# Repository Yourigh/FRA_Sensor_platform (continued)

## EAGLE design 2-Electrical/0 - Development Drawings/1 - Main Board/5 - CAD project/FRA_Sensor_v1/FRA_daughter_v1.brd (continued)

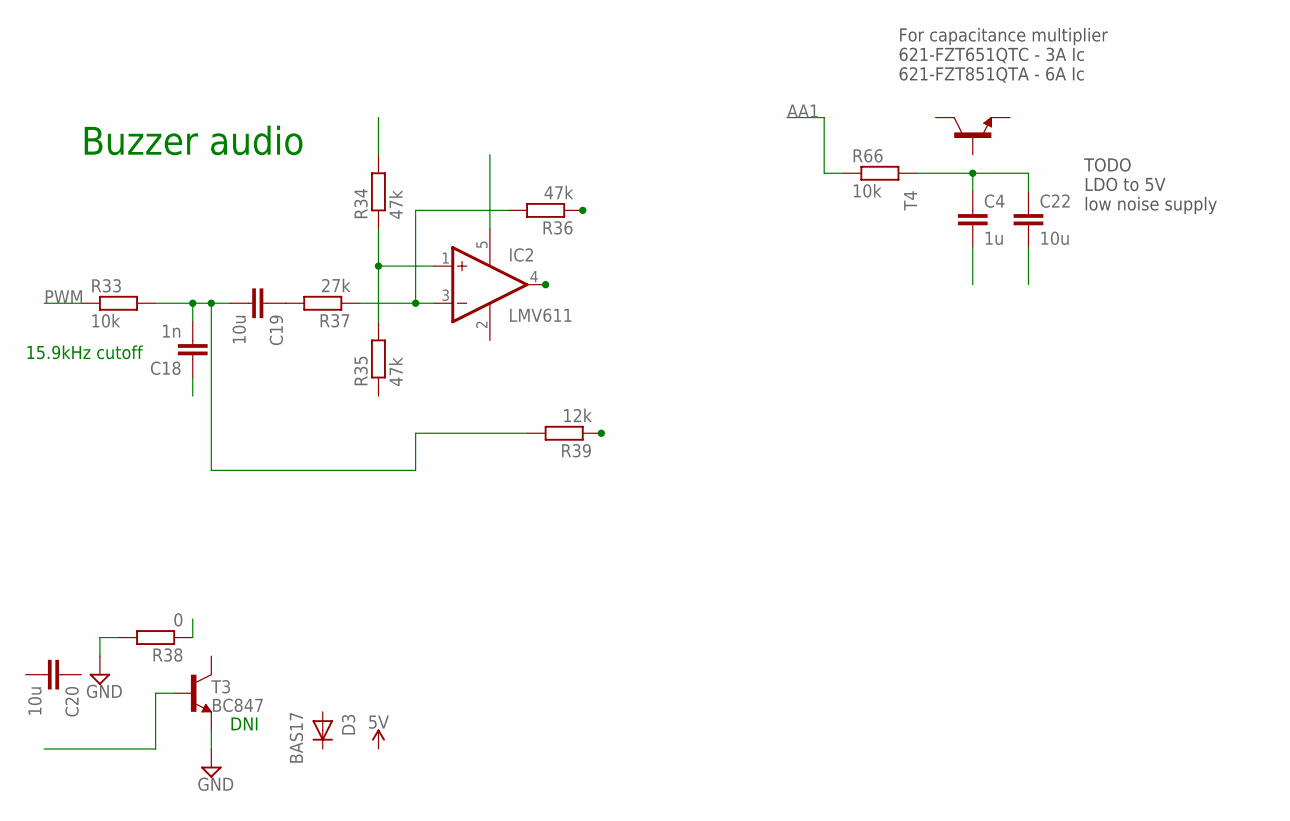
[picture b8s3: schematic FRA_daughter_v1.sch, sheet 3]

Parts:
C4: 1u; C0603K
C18: 1n; C0603K
C19, C20, C22: 10u; C0603K
D3: BAS17; SOT23
IC2: LMV611; SC70-5L
R33, R66: 10k; R0603
R34, R35, R36: 47k; R0603
R37: 27k; R0603
R38: 0; R0603
R39: 12k; R0603
T3: BC847; SOT23
T4: -NPN-SOT223; SOT223

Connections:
AA1: R66.1
GND: R38.2, T3.2 (E); also elsewhere on the board
unnamed: C4.1, C22.1, R66.2
unnamed: R39.1, T3.1 (B)
unnamed: IC2.1 (+IN), R34.1, R35.2
unnamed: IC2.3 (-IN), R36.2, R37.1
unnamed: C19.1, R37.2
unnamed: IC2.4 (OUT), R36.1
unnamed: C18.2, C19.2, R33.2, R39.2
PWM: R33.1
V-: IC2.2 (V-)

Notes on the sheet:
15.9kHz cutoff
Buzzer audio
DNI
For capacitance multiplier 621-FZT651QTC - 3A Ic 621-FZT851QTA - 6A Ic
TODO LDO to 5V low noise supply

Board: 2 copper layers, 34 parts (0 on the bottom side), 16 nets, no tracks yet.

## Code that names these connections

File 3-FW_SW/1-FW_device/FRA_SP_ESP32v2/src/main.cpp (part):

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#include <esp_task_wdt.h>

//custom pins
#define PIN_ETH_INT 36 //was 2, changed due to FW loading problems
#define PIN_ETH_NRST 4
#define PIN_LED 16
#define PIN_SD_CS  17  // SD chip select pin
#define PIN_SDA 21
#define PIN_SCL 22
#define PIN_ETH_CS 23
#define PIN_FAN 25
#define PIN_TP8 26 //used as fake SDA for real SDA line manipulation
#define PIN_TP9 27
#define PIN_BTN1 34
#define PIN_TP7 36
#define PIN_TP6 39
//custom parameters
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
void setup(){
  error_code[0] = 0;
  pinMode(PIN_BTN1,INPUT);
  attachInterrupt(digitalPinToInterrupt(PIN_BTN1), ISR_BTN1, FALLING);
  pinMode(PIN_ETH_INT,INPUT);
  pinMode(PIN_ETH_NRST,OUTPUT);
  digitalWrite(PIN_ETH_NRST,0);
  pinMode(PIN_LED,OUTPUT); //LED on final HW
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  esp_efuse_read_mac(chipid);
  chipid[5]++; //use MAC address for ETH one larger than WiFi MAC (WiFi MAC is chip ID)
  // Change 'SS' to your Slave Select pin, if you arn't using the default pin
  if (ether.begin(sizeof Ethernet::buffer, chipid, PIN_ETH_CS) == 0){
    Serial.println(F("Failed to access Ethernet controller"));
    log_error_code(1);
  }
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  // Initialize at the highest speed supported by the board that is
  // not over 50 MHz. Try a lower speed if SPI errors occur.
  use_sd = 1;
  if (!sd.begin(PIN_SD_CS, SD_SCK_MHZ(20))) {  //SPI clock , 50MHz or 40M does not wrok, 20M ok, 
    sd.initErrorHalt(); //halt turned off, but will give logs to serial
    use_sd=0;
    log_error_code(3);
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  uint32_t adc_period_ms = 1000; //every X ms 
  uint8_t adc_PGA_setting[3][4]; //ADC is first index, ch second
  int16_t adc_result_raw[3][4]; //result [ADC][channel]
  uint32_t meas_sample_number = 0; //0 is measurement not active, from 1 on - sample number
  uint8_t port0_check;
  uint8_t port1_check;
  uint8_t conf_set = 0; // raw received configuration set byte
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    //this must be called for ethercard functions to work. 
    //Returns Length of received data. If non-zero, something is coming.
    if (UDP_read_flag == 0) //if receive buffer ready for data, check if thre is incoming DTG
      if (digitalRead(PIN_ETH_INT)==0){ //if interrupt of incoming data or want to send data
        ether.packetLoop(ether.packetReceive()); //Returns Length of received data. If non-zero, something is coming.
      }
      //data were already processed and put into receiveUDP_buffer.
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        } 
        if (uint16_t(millis()) > (startms + 30000)){break;}  //30s timeout
        
        if (digitalRead(PIN_BTN1)){break;} //released button
        
        if (millis()-startms < 1000){
          //PRINTDEBUG("Pressed under 1s, nothing happens\n");
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
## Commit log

2019-05-03 UDP demo working
2019-05-04 block diagram
2019-05-04 project setup, 2 sensors in library
2019-05-04 sensor data
2019-05-05 TGS2611 integration
2019-05-06 programming interface ready
2019-05-07 project setup esp32
2019-05-08 connection update, debugger setup-now working
2019-05-08 ESP32v2 debugger running, UDP receiving
2019-05-08 not working project copy deleted
2019-05-10 SCH update
2019-05-12 power circuits
2019-05-14 UDP sender done
2019-05-18 SD card connected
2019-05-22 dev and sd
    mac address changed
    other sample testing
    sd card example setup
2019-05-22 gitignore update
2019-05-24 SD card logging test working
    SPI speed had to be decreased
2019-05-24 placment drafts
2019-05-25 write time analysis
2019-05-25 digital sensors interface
2019-05-26 VI and esp communication
2019-05-28 labview ACKs
2019-06-04 sch and layiout
2019-06-04 jtag layout
2019-06-05 power layouts
2019-06-09 sch cap miltuplier add
2019-06-16 sensor datasheets
2019-06-19 datasheets, sch update
2019-06-24 ldo addded
2019-06-27 sch update
    layout, od powerm SPIs,
2019-07-12 sch update layout update
2019-07-13 layout done,
2019-07-17 SD and ethernet merged
2019-07-17 resources update
2019-07-18 gpio expander init and all low functions
2019-07-18 adc integrated, 2 ADCs tested
2019-07-18 define custom pins, added broadcast frist for announcement of unit
2019-07-20 announcements, io expander, ...
2019-07-20 docs
2019-07-24 power reports done, interrupt ethernet..
2019-07-25 boad update v2
2019-07-25 error code array instead one value
2019-07-26 error report fixed and sw reset done
2019-07-27 fixed network, ADC begin
2019-07-29 sch main final touches
2019-07-30 sensor board sch and layout
2019-07-31 BOM updates, labview
2019-08-01 sd card logging done
2019-08-02 Light sensor integrated
2019-08-06 updates
    amonia sensor
    preparation for LMP91000
    ADC1 address changed to match V4 board
2019-08-07 data saving fixes, ADC address changed
2019-08-09 dev for LMP91000
2019-08-09 sensor board update, main VI update
2019-08-16 hw design updates
2019-08-17 amonia sensor tuning
2019-08-18 TGS board update
2019-08-18 electrochemical board design
2019-08-19 updates spec
2019-08-20 programing procedure, elchem board
2019-08-20 flash guide
2019-08-20 LMP code align
2019-08-20 versioning start
2019-08-20 full SD card check
2019-08-20 cleanup
2019-08-20 csv sync to git
2019-08-21 legends fix
2019-08-22 sensor tests
2019-08-23 sensor elchem testing, reports, code update
2019-08-23 electrochemical sensors test results
2019-08-27 data processing, orders review, tests, elchem pcb RE CE swap
2019-08-29 mhm01 board
2019-09-03 BOM updates
2019-09-04 manufacuting pics
2019-09-04 incorrect pics removed
2019-09-07 labview miltiple unit selection
2019-09-07 update of conf. sets
2019-09-10 MHM labview script update
2019-10-04 data converter work
2019-10-05 data converster from labview log done
2019-10-07 converter update
2019-10-08 converter to app specific values
2019-10-10 baseline converter
2019-10-10 converter SD card log too
2019-10-29 silkscreen update
2019-11-01 converter build exe
2019-11-02 V1.4 update conf set
2019-11-06 build exe for logger pc app
2019-11-06 bugfix, logger exe release path to DATA folder
2019-11-06 bug fix A1.3 REFCN register
2019-11-23 bug fix app spec converter
2019-11-30 added sdfat, searching for issues
2019-11-30 CS ETH pin change
2019-11-30 removed restart on EEPROM init fail
    even if eeprom fails to init, things seem to work well.
2019-11-30 LW app, runtime bux fix error database
2019-12-04 button stop measurement fcn, static fallback IP, V1.7 release
2019-12-04 added pics
2019-12-04 resized images
2019-12-04 images to readme
2019-12-06 3d export
2019-12-06 3D model created
2019-12-14 ME box project setup
2020-03-04 junction board
2020-03-04 manuf data junction b
2020-03-07 bulkhead board
2020-03-18 bulkhead design, updated confsets added 7th
2020-10-21 added picture from test
2020-12-03 edited ESP32 footprint
2020-12-03 generated gerber data
2020-12-04 silkscreen edits on breakout boards
2021-06-01 add sample images
2021-06-01 Create FRA-FW.code-workspace
2021-06-02 edited configuration sets. V1.8 FW
2021-09-27 flash procedure updated, Labview app update
    *convert data live in preview graphs
    *make special conversions and integrations in graph D - enabled in dot tab.
2021-09-28 removed unzipped builds
2022-12-21 Added framework and libraries version. For new version, I2C and MAC need to be updated.
2023-08-10 New configuration for elchem. Removed amonia from FW. Updated flash guide debug. New FW release.
2023-08-10 Labview app update - removed amonia, fixed formatting, graphics.
2023-10-13 add NDIR module support. FW code cleanup.
